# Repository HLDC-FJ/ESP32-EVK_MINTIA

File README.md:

# ESP32 EVK for MINTIA
MINTIA (清涼菓子) ケースを使用し、ESP32 EVK作成を行う。

* ESP32
* Acconeer XM125 (60GHz Radar)
* IR Sensor Array

MINTIAケースを活かし素敵な EVK を作る

このプロジェクトは、ソフトウェアとハードウェアの両方を含みます。
以下のコンポーネントは MIT ライセンスの下で公開されています。

- ソフトウェア（コード、スクリプトなど）
- ハードウェア設計（回路図、基板データ、CADファイルなど）

## ライセンス
このプロジェクトは MIT ライセンスの下で提供されています。  
詳細は [LICENSE](./License.md) ファイルを参照してください。

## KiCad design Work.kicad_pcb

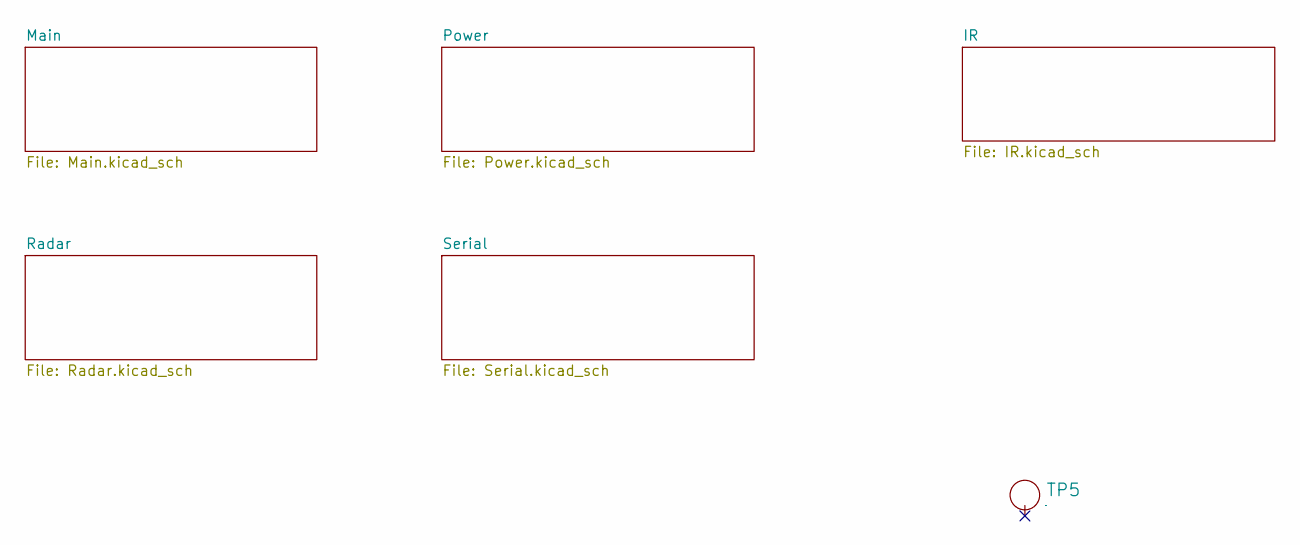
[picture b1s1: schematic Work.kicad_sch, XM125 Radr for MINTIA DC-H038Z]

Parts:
TP5: TP_FL; HLDC_logo2

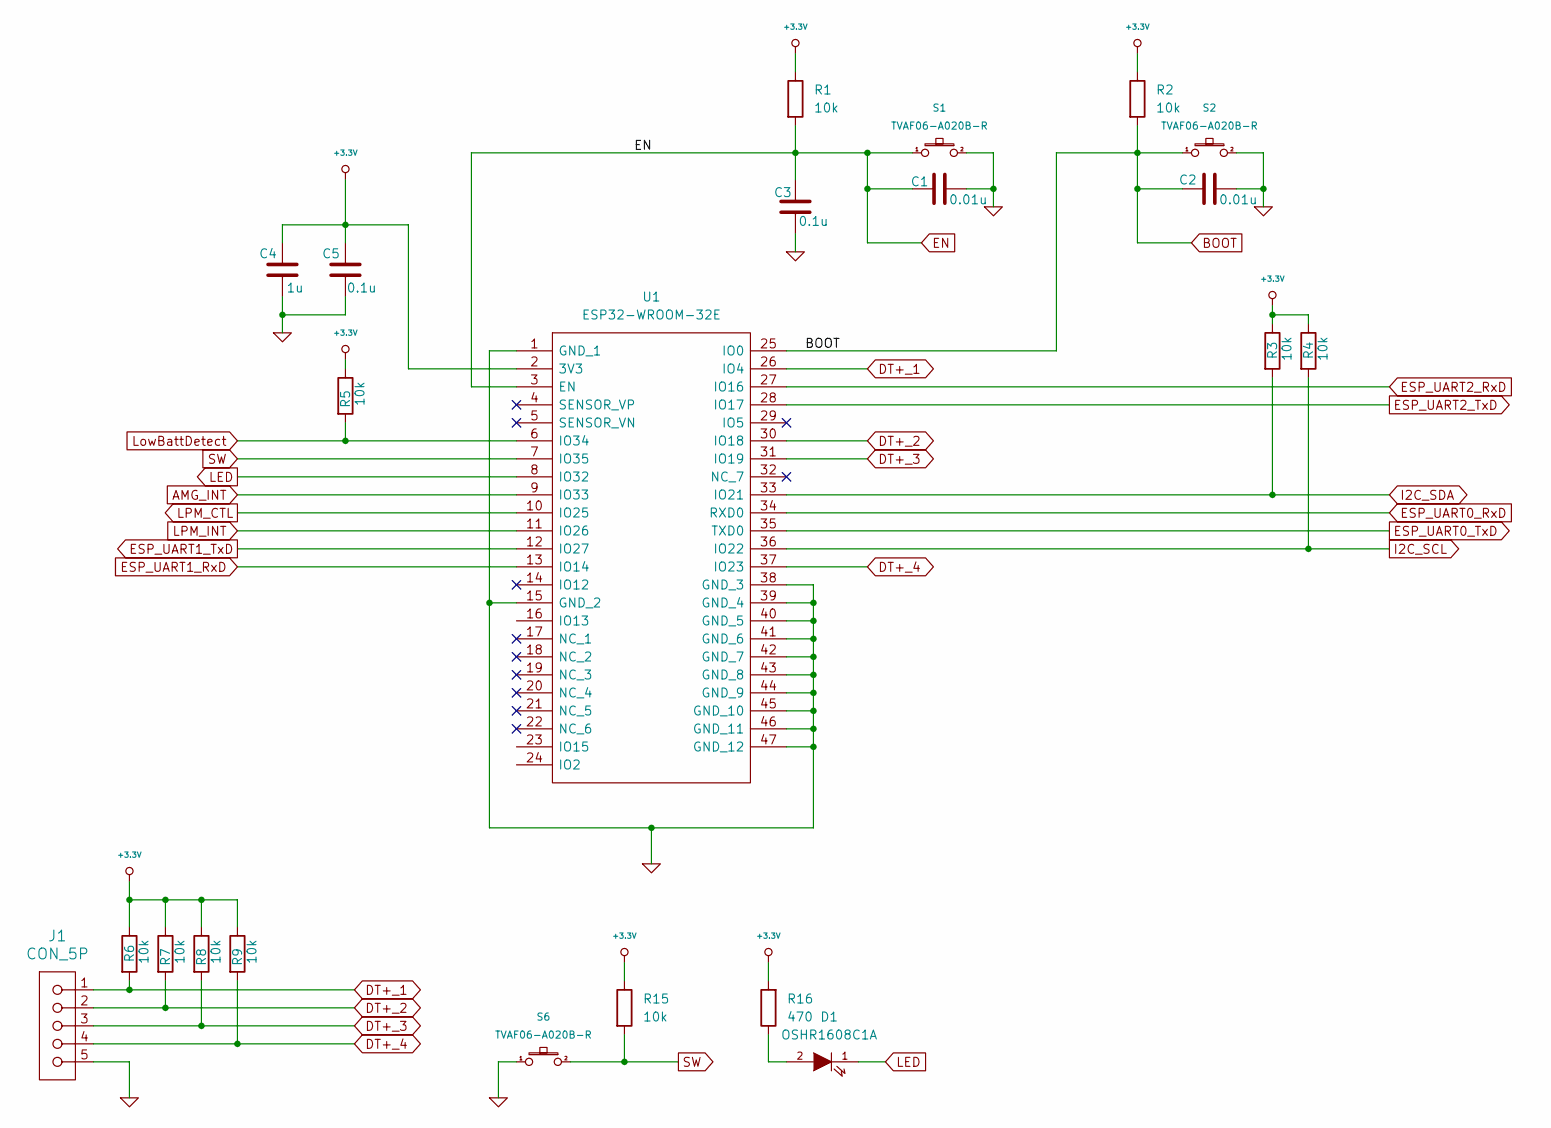
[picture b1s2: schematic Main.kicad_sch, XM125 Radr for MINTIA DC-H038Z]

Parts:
C1, C2: 0.01u; C_0603_1608Metric; PARTNUMBER GRM1882C1H103JA01
C3, C5: 0.1u; C_0603_1608Metric; PARTNUMBER GRM188R72A104MA35
C4: 1u; C_0603_1608Metric; PARTNUMBER GRM185R61C105KE44
D1: OSHR1608C1A; D_0603; PARTNUMBER OSHR1608C1A
J1: CON_5P; CONN_S5B-ZR_JST; PARTNUMBER S5B-ZR
R1, R2, R3, R4, R5, R6, R7, R8, R9, R15: 10k; R_0603_1608Metric; PARTNUMBER ERJ3GEYJ103V
R16: 470; R_0603_1608Metric; PARTNUMBER ERJ3GEYJ471V
S1, S2, S6: TVAF06-A020B-R; TVAF06A020BR; PARTNUMBER TVAF06-A020B-R
U1: ESP32-WROOM-32E; ESP32WROOM32E-Hole; Manufacturer_Part_Number ESP32-WROOM-32E

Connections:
+3.3V: C4.2, C5.2, R1.1, R2.1, R3.1, R4.1, R5.1, R6.1, R7.1, R8.1, R9.1, R15.1, R16.2, U1.2 (3V3); also elsewhere on the board
AMG_INT: U1.9 (IO33); also elsewhere on the board
BOOT: C2.2, R2.2, S2.1, U1.25 (IO0); also elsewhere on the board
DT+_1: J1.1, R6.2, U1.26 (IO4)
DT+_2: J1.2, R7.2, U1.30 (IO18)
DT+_3: J1.3, R8.2, U1.31 (IO19)
DT+_4: J1.4, R9.2, U1.37 (IO23)
EN: C1.2, C3.1, R1.2, S1.1, U1.3 (EN); also elsewhere on the board
ESP_UART0_RxD: U1.34 (RXD0); also elsewhere on the board
ESP_UART0_TxD: U1.35 (TXD0); also elsewhere on the board
ESP_UART1_RxD: U1.13 (IO14); also elsewhere on the board
ESP_UART1_TxD: U1.12 (IO27); also elsewhere on the board
ESP_UART2_RxD: U1.27 (IO16); also elsewhere on the board
ESP_UART2_TxD: U1.28 (IO17); also elsewhere on the board
GND: C1.1, C2.1, C3.2, C4.1, C5.1, J1.5, S1.2, S2.2, S6.1, U1.1 (GND_1), U1.15 (GND_2), U1.38 (GND_3), U1.39 (GND_4), U1.40 (GND_5), U1.41 (GND_6), U1.42 (GND_7), U1.43 (GND_8), U1.44 (GND_9), U1.45 (GND_10), U1.46 (GND_11), U1.47 (GND_12); also elsewhere on the board
I2C_SCL: R4.2, U1.36 (IO22); also elsewhere on the board
I2C_SDA: R3.2, U1.33 (IO21); also elsewhere on the board
LED: D1.1 (K), U1.8 (IO32)
LPM_CTL: U1.10 (IO25); also elsewhere on the board
LPM_INT: U1.11 (IO26); also elsewhere on the board
LowBattDetect: R5.2, U1.6 (IO34)
unnamed: D1.2 (A), R16.1
SW: R15.2, S6.2, U1.7 (IO35)

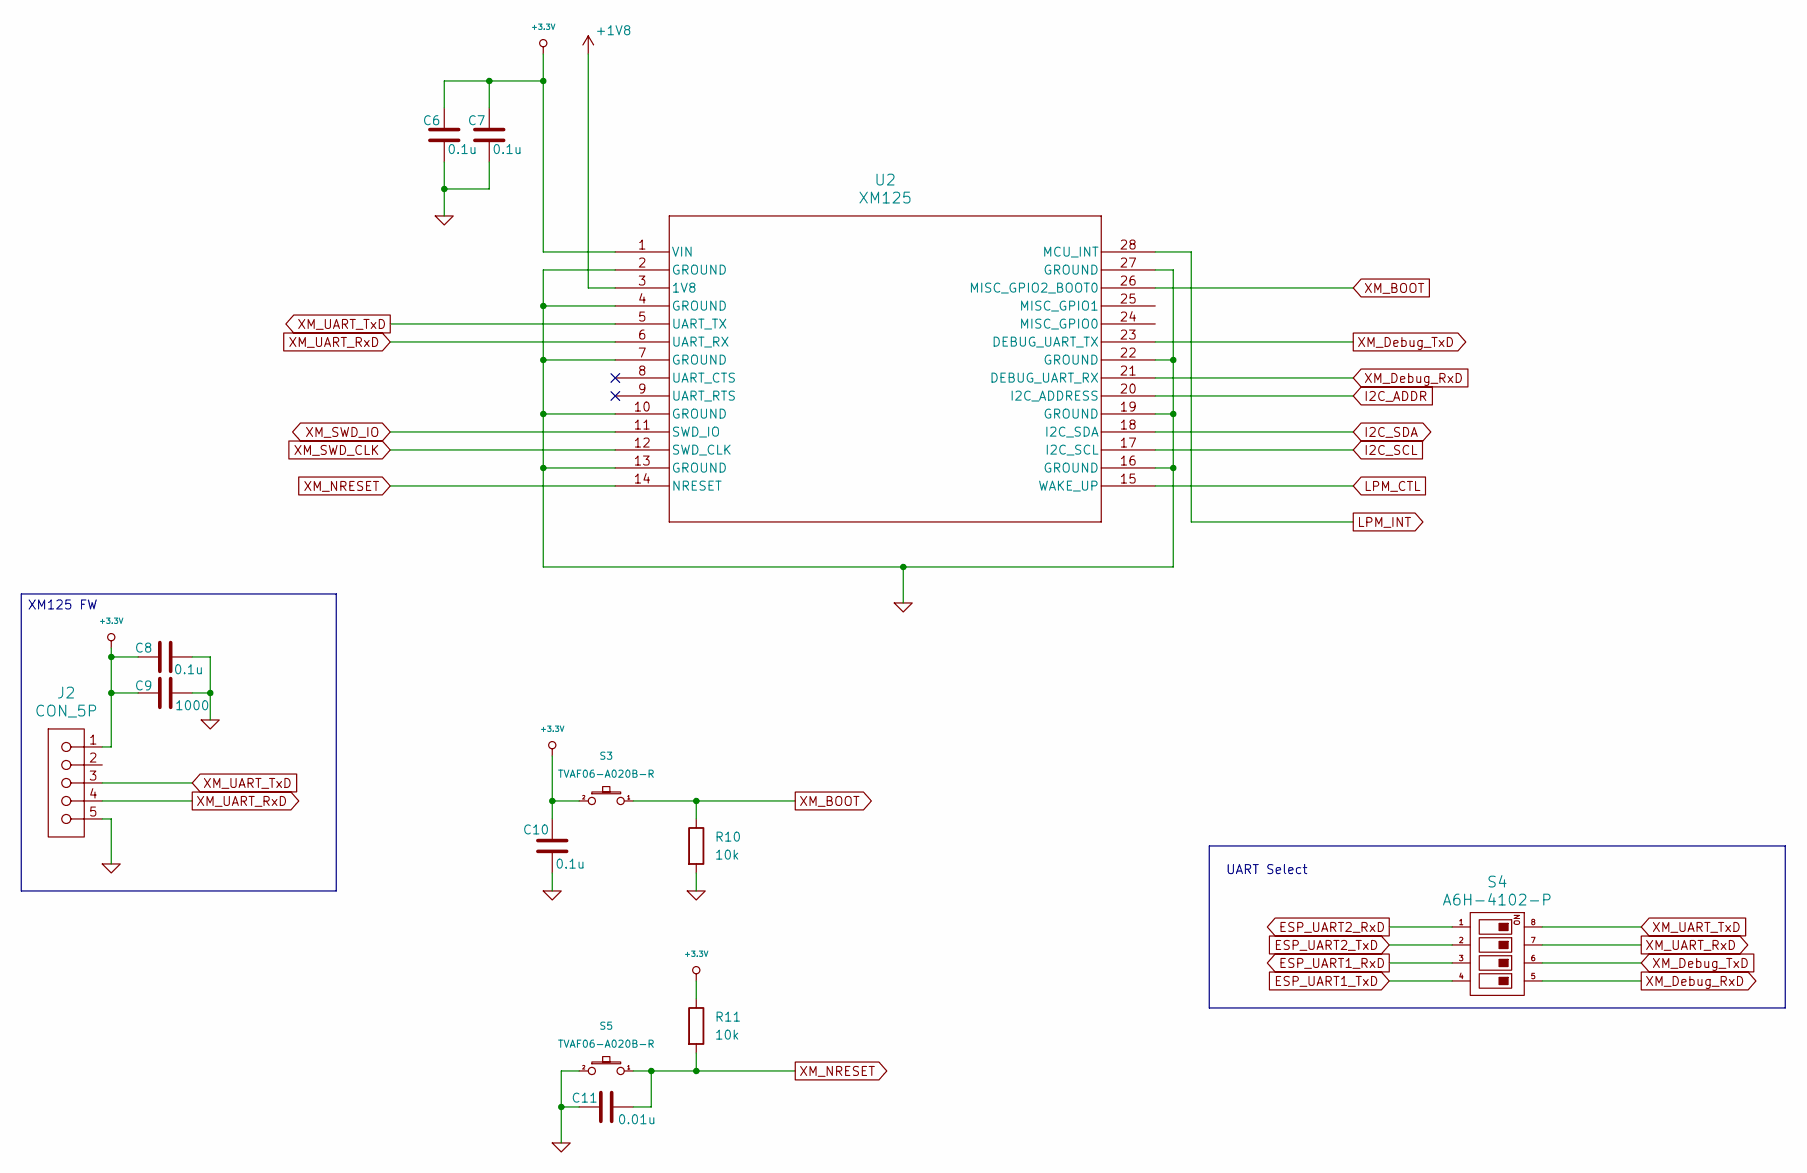
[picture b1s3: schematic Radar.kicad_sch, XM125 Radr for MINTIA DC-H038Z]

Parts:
C6, C7, C8, C10: 0.1u; C_0603_1608Metric; PARTNUMBER GRM188R72A104MA35
C9: 1000; C_0603_1608Metric; PARTNUMBER GRM1882C1H102JA01
C11: 0.01u; C_0603_1608Metric; PARTNUMBER GRM1882C1H103JA01
J2: CON_5P; CONN_S5B-ZR_JST; PARTNUMBER S5B-ZR
R10, R11: 10k; R_0603_1608Metric; PARTNUMBER ERJ3GEYJ103V
S3, S5: TVAF06-A020B-R; TVAF06A020BR; PARTNUMBER TVAF06-A020B-R
S4: A6H-4102-P; SW_DIP_SPSTx04_Slide_Omron_A6H-4101_W6.15mm_P1.27mm; PARTNUMBER A6H-4102-P
U2: XM125; XM125_ACC; PARTNUMBER XM125

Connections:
+1V8: U2.3 (1V8); also elsewhere on the board
+3.3V: C6.1, C7.1, C8.2, C9.2, C10.1, J2.1, R11.1, S3.2, U2.1 (VIN); also elsewhere on the board
ESP_UART1_RxD: S4.3; also elsewhere on the board
ESP_UART1_TxD: S4.4; also elsewhere on the board
ESP_UART2_RxD: S4.1; also elsewhere on the board
ESP_UART2_TxD: S4.2; also elsewhere on the board
GND: C6.2, C7.2, C8.1, C9.1, C10.2, C11.2, J2.5, R10.2, S5.2, U2.2 (GROUND), U2.4 (GROUND), U2.7 (GROUND), U2.10 (GROUND), U2.13 (GROUND), U2.16 (GROUND), U2.19 (GROUND), U2.22 (GROUND), U2.27 (GROUND); also elsewhere on the board
I2C_ADDR: U2.20 (I2C_ADDRESS)
I2C_SCL: U2.17 (I2C_SCL); also elsewhere on the board
I2C_SDA: U2.18 (I2C_SDA); also elsewhere on the board
LPM_CTL: U2.15 (WAKE_UP); also elsewhere on the board
LPM_INT: U2.28 (MCU_INT); also elsewhere on the board
XM_BOOT: R10.1, S3.1, U2.26 (MISC_GPIO2_BOOT0)
XM_Debug_RxD: S4.5, U2.21 (DEBUG_UART_RX)
XM_Debug_TxD: S4.6, U2.23 (DEBUG_UART_TX)
XM_NRESET: C11.1, R11.2, S5.1, U2.14 (NRESET)
XM_SWD_CLK: U2.12 (SWD_CLK)
XM_SWD_IO: U2.11 (SWD_IO)
XM_UART_RxD: J2.4, S4.7, U2.6 (UART_RX)
XM_UART_TxD: J2.3, S4.8, U2.5 (UART_TX)

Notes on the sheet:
UART Select
XM125 FW

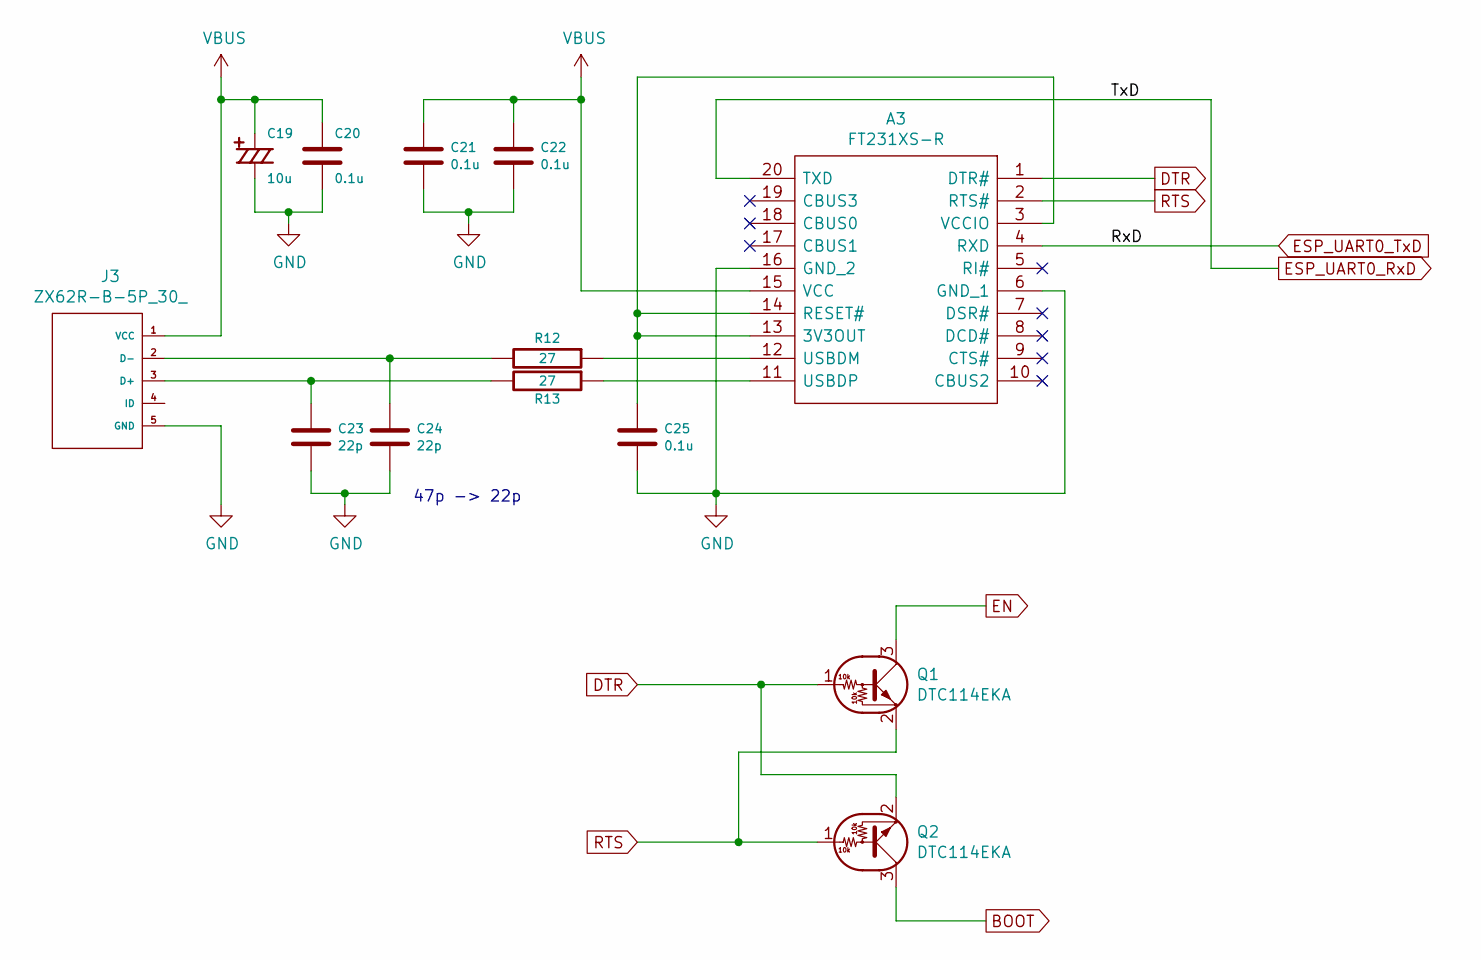
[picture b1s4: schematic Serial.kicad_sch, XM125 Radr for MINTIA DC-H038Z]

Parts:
A3: FT231XS-R; SOP64P599X175-20N; Manufacturer_Part_Number FT231XS-R
C19: 10u; F920J106MPA; PARTNUMBER F920J106MPA
C20, C21, C22, C25: 0.1u; C_0603_1608Metric; PARTNUMBER GRM188R72A104MA35
C23, C24: 22p; C_0603_1608Metric; PARTNUMBER GRM1885C2E220FW07
J3: ZX62R-B-5P_30_; ZX62R-B-5P_30; PARTNUMBER ZX62R-B-5P(30)
Q1, Q2: DTC114EKA; SC-59; PARTNUMBER DTC114EKA
R12, R13: 27; R_0603_1608Metric; PARTNUMBER ERJ3GEYJ270V

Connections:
BOOT: Q2.3 (C); also elsewhere on the board
DTR: A3.1 (DTR#), Q1.1 (B), Q2.2 (E)
EN: Q1.3 (C); also elsewhere on the board
ESP_UART0_RxD: A3.20 (TXD); also elsewhere on the board
ESP_UART0_TxD: A3.4 (RXD); also elsewhere on the board
GND: A3.6 (GND_1), A3.16 (GND_2), C19.2, C20.2, C21.2, C22.2, C23.2, C24.2, C25.2, J3.5 (GND); also elsewhere on the board
unnamed: A3.3 (VCCIO), A3.13 (3V3OUT), A3.14 (RESET#), C25.1
unnamed: A3.12 (USBDM), R12.1
unnamed: A3.11 (USBDP), R13.1
unnamed: C23.1, J3.3 (D+), R13.2
unnamed: C24.1, J3.2 (D-), R12.2
RTS: A3.2 (RTS#), Q1.2 (E), Q2.1 (B)
VBUS: A3.15 (VCC), C19.1, C20.1, C21.1, C22.1, J3.1 (VCC); also elsewhere on the board

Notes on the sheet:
47p -> 22p

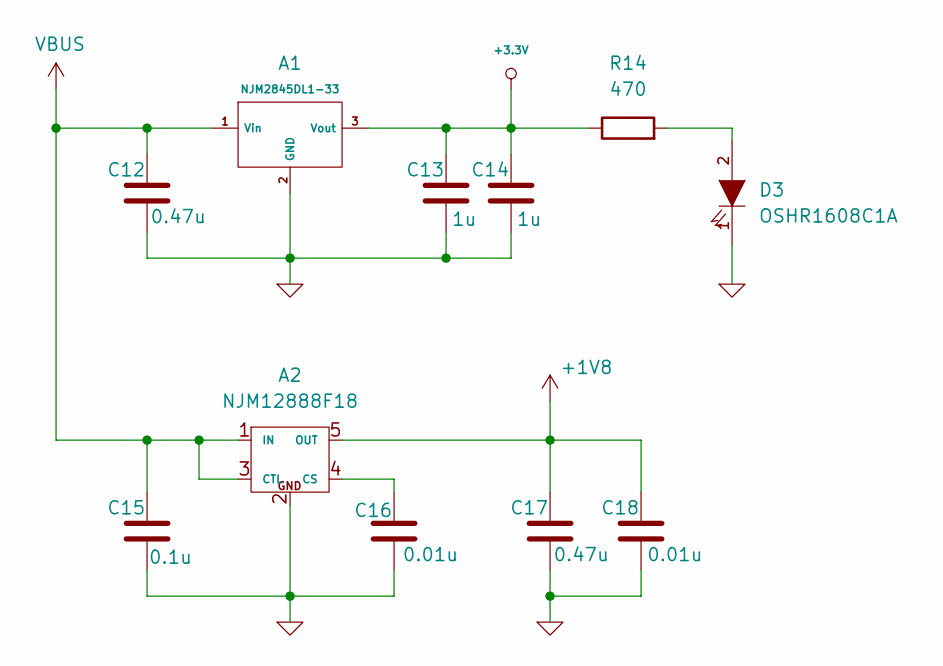
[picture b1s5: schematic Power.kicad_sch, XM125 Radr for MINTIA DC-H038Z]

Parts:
A1: NJM2845DL1-33; TO-252-2; PARTNUMBER NJM2845DL1-33
A2: NJM12888F18; SOT-23-5; PARTNUMBER NJM12888F18
C12, C17: 0.47u; C_0603_1608Metric; PARTNUMBER GRM188R71C474KA88
C13, C14: 1u; C_0603_1608Metric; PARTNUMBER GRM185R61C105KE44
C15: 0.1u; C_0603_1608Metric; PARTNUMBER GRM188R72A104MA35
C16, C18: 0.01u; C_0603_1608Metric; PARTNUMBER GRM1882C1H103JA01
D3: OSHR1608C1A; D_0603; PARTNUMBER OSHR1608C1A
R14: 470; R_0603_1608Metric; PARTNUMBER ERJ3GEYJ471V

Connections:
+1V8: A2.5 (OUT), C17.2, C18.2; also elsewhere on the board
+3.3V: A1.3 (Vout), C13.2, C14.2, R14.1; also elsewhere on the board
GND: A1.2 (GND), A2.2 (GND), C12.1, C13.1, C14.1, C15.1, C16.1, C17.1, C18.1, D3.1 (K); also elsewhere on the board
unnamed: A2.4 (CS), C16.2
unnamed: D3.2 (A), R14.2
VBUS: A1.1 (Vin), A2.1 (IN), A2.3 (CTL), C12.2, C15.2; also elsewhere on the board

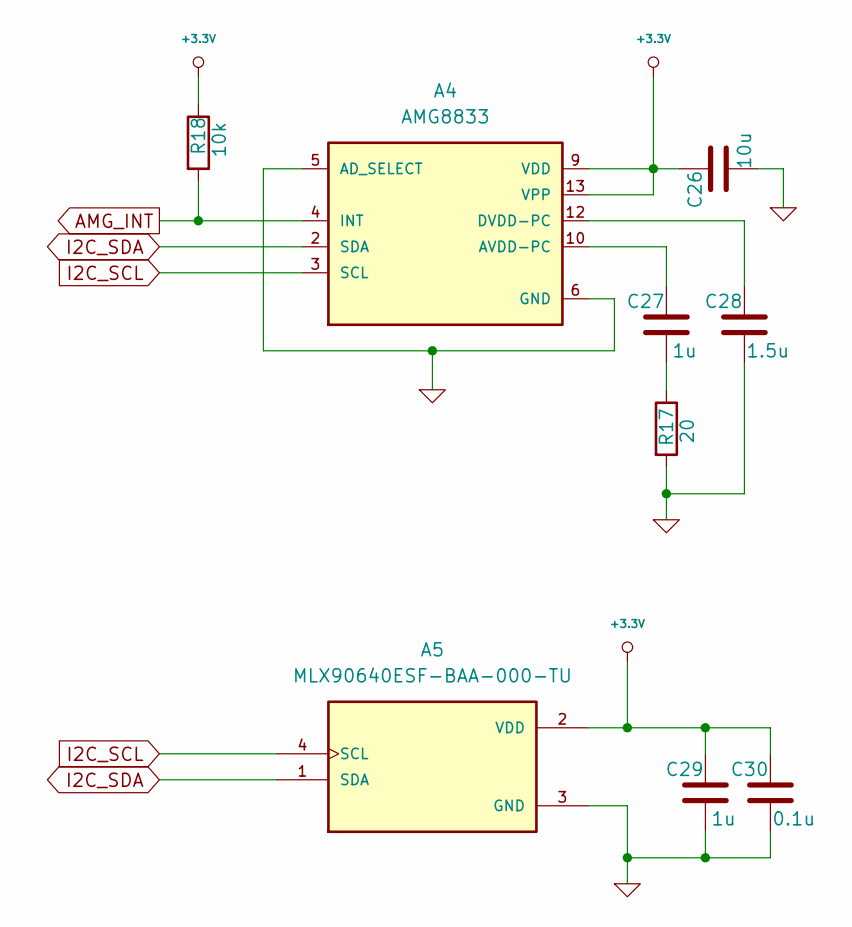
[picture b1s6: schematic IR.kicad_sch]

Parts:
A4: AMG8833; XDCR_AMG8833; PARTNUMBER AMG8833
A5: MLX90640ESF-BAA-000-TU; TO292P930H600-4; PARTREV 11
C26: 10u; C_0603_1608Metric; PARTNUMBER GRM188C81C106MA73
C27, C29: 1u; C_0603_1608Metric; PARTNUMBER GRM185R61C105KE44
C28: 1.5u; C_0603_1608Metric; PARTNUMBER CGA3E1X5R1C155K080AC
C30: 0.1u; C_0603_1608Metric; PARTNUMBER GRM188R72A104MA35
R17: 20; R_0603_1608Metric; PARTNUMBER ERJ3GEYJ200V
R18: 10k; R_0603_1608Metric; PARTNUMBER ERJ3GEYJ103V

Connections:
+3.3V: A4.9 (VDD), A4.13 (VPP), A5.2 (VDD), C26.2, C29.2, C30.2, R18.1; also elsewhere on the board
AMG_INT: A4.4 (INT), R18.2; also elsewhere on the board
GND: A4.5 (AD_SELECT), A4.6 (GND), A5.3 (GND), C26.1, C28.1, C29.1, C30.1, R17.2; also elsewhere on the board
I2C_SCL: A4.3 (SCL), A5.4 (SCL); also elsewhere on the board
I2C_SDA: A4.2 (SDA), A5.1 (SDA); also elsewhere on the board
unnamed: A4.10 (AVDD-PC), C27.2
unnamed: A4.12 (DVDD-PC), C28.2
unnamed: C27.1, R17.1

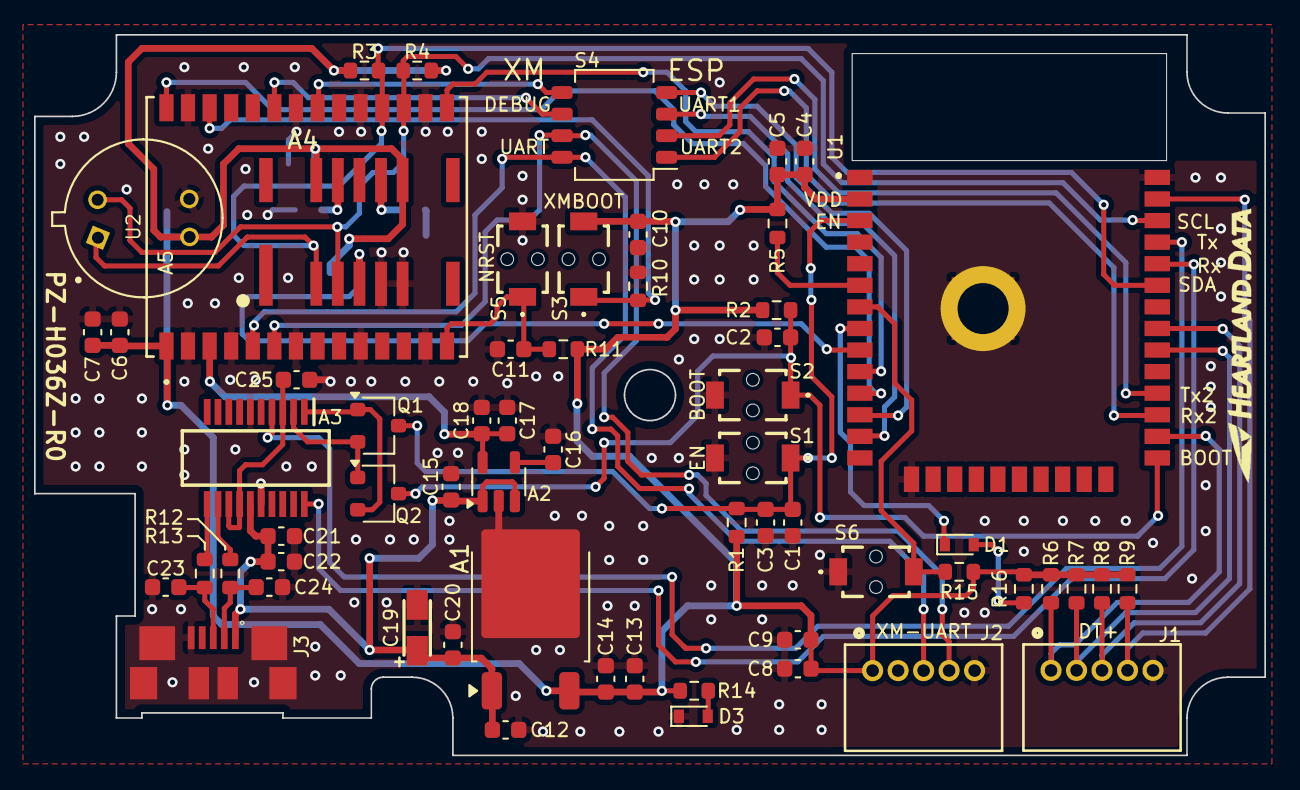
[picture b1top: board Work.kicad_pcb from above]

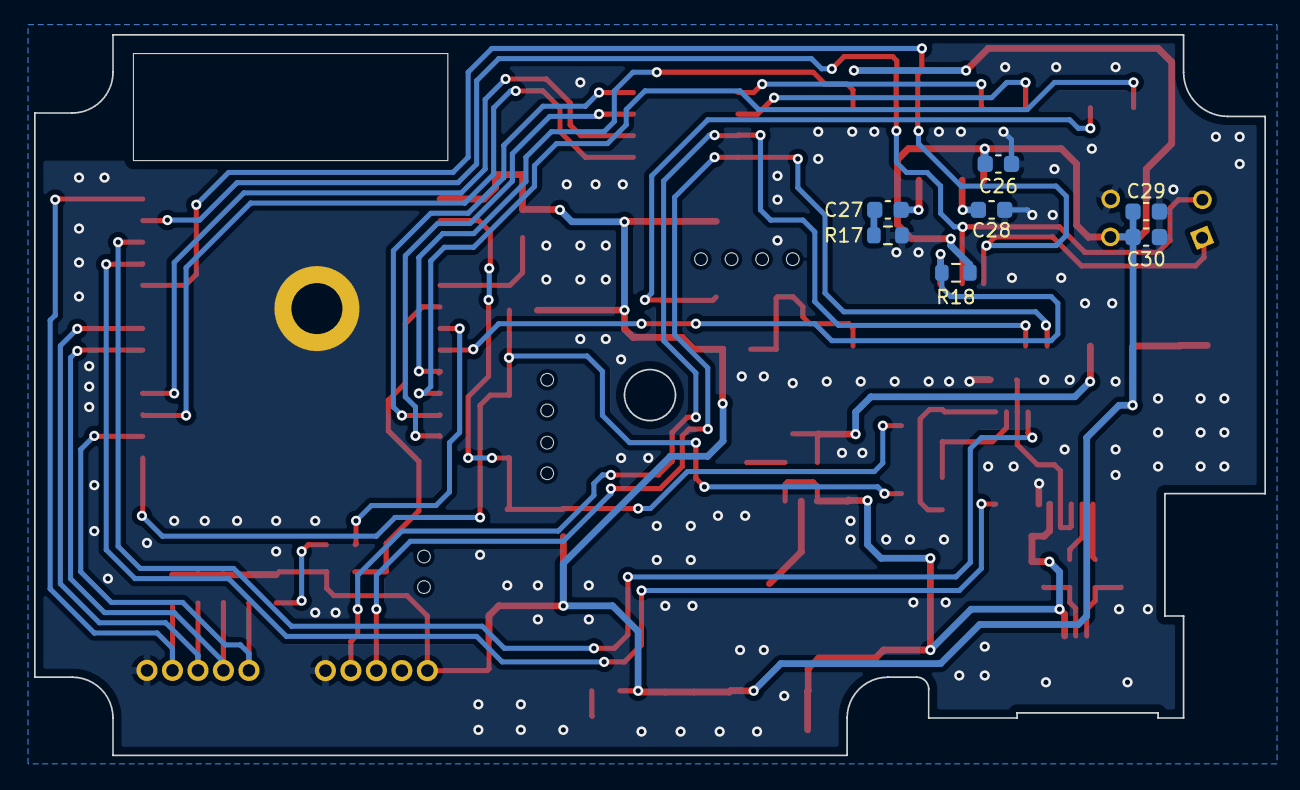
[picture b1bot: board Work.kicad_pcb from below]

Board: 2 copper layers, 72.4 x 42.4 mm, 69 parts (7 on the bottom side), 43 nets.

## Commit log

2025-06-06 Edge Cut Data
2025-06-09 SCH & PCB Data
2025-06-18 DIP SW Pad Change
2025-06-18 Gerber Data
2025-06-18 Revision change
